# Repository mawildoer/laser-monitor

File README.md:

# Laser Monitor

A pair of IR diodes for monitoring laser reflectance

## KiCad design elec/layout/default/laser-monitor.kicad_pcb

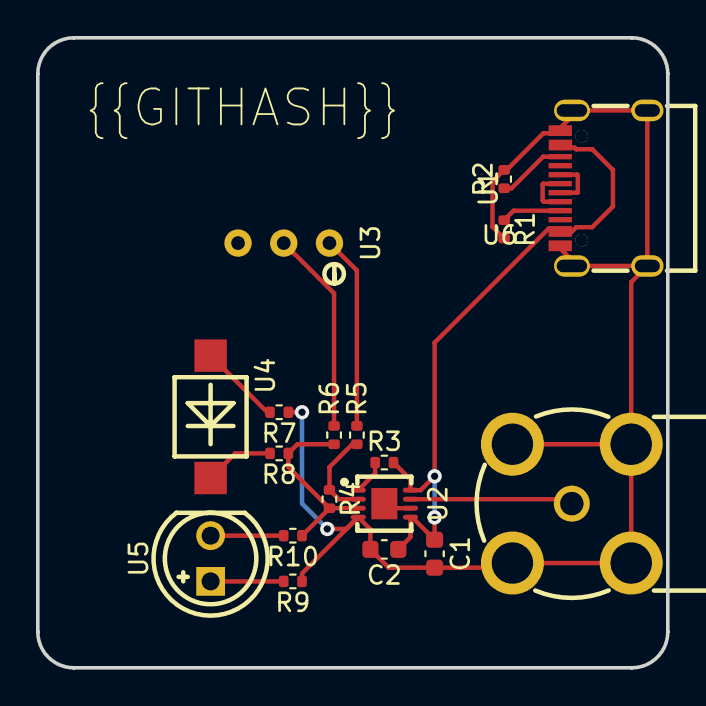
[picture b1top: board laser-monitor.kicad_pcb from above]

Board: 2 copper layers, 35.0 x 35.0 mm, 18 parts (0 on the bottom side), 16 nets.

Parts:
C1, C2: 50V 100nF X7R ±10% 0603 Multilayer Ceramic Capaci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; C0603
R1, R2: 62.5mW Thick Film Resistors 50V ±100ppm/℃ ±1% 5.1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; R0402
R3: 62.5mW Thick Film Resistors 50V ±100ppm/℃ ±1% 10k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; R0402
R4: 62.5mW Thick Film Resistors 50V ±100ppm/℃ ±1% 249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; R0402
R5, R6, R7, R8, R9, R10: 62.5mW Thick Film Resistors 50V ±800ppm/℃ ±1% 0Ω 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; R0402
U1: ?; USB-C-SMD_KH-TYPE-C-16P
U2: ?; LFCSP-8_L3.0-W3.0-P0.50-BL-EP-1
U3: ?; RES-ADJ-TH_3296W
U4: ?; SENSOR-SMD_L4.4-W3.9
U5: ?; LED-TH_BD5.8-P2.54-FD
U6: ?; BNC-TH_DOSIN-801-0051

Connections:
amp-b: R4.2, R6.1, R8.1, R10.1, U2.3
cc1: R1.1, U1.A5
cc2: R2.1, U1.B5
dm: U1.A7, U1.B7
dp: U1.A6, U1.B6
fb: R4.1, R5.1, U2.2
out: U2.7, U6.5
photodiode1-a_t: R7.2, U4.1
photodiode1-b_t: R8.2, U4.2
photodiode2-a_t: R9.2, U5.1
photodiode2-b_t: R10.2, U5.2
sleep: R3.1, U2.1
trim_pot-a_t: R5.2, U3.1
trim_pot-b_t: R6.2, U3.2
usb-gnd: C1.2, C2.2, R1.2, R2.2, R7.1, R9.1, U1.1, U1.2, U1.3, U1.4, U1.A1, U1.A12, U1.B1, U1.B12, U2.4, U6.1, U6.2, U6.3, U6.4
vcc: C1.1, C2.1, R3.2, U1.A4, U1.A9, U1.B4, U1.B9, U2.5, U2.8

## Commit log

2024-10-09 Init together
2024-10-09 Done
